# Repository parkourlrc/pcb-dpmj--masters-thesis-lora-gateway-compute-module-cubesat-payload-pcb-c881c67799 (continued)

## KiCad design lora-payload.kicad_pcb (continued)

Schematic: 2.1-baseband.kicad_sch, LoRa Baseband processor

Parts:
C701, C703, C705, C706, C707, C709, C711, C712, C713: 0.1uF; C_0402_1005Metric; PartNumber GRM155R71C104KA88J
C702, C704, C708, C710: 1uF; C_0402_1005Metric; PartNumber GRM155Z71A105KE01J
D701: D_Schottky; D_SOD-882
D702, D703, D704: Green; LED_0402_1005Metric
R701, R704, R705: 47 kOhms; R_0402_1005Metric; PartNumber RC0402FR-0747KL
R702: 10 Ohms; R_0402_1005Metric; PartNumber RC0402FR-0710RL
R703: 100 Ohms; R_0402_1005Metric; PartNumber RC0402FR-07100RL
R706, R708, R709: 680 Ohms; R_0402_1005Metric
R707, R712: 33 Ohms; R_0402_1005Metric; PartNumber AC0402FR-0733RL
R710, R711: 4.7 kOhms; R_0402_1005Metric; PartNumber RC0402FR-074K7L
RN701, RN702: 33 Ohms; R_Array_Convex_4x0603; PartNumber YC164-FR-0733RL
TP701, TP702, TP703, TP704, TP705, TP706, TP707, TP708, TP709, TP710, TP711, TP712: TestPoint; TestPoint_Pad_D1.0mm
U701: SX1302IMLTRT; Semtech SX1302 QFN-68-1EP_7x7mm_P0.35mm_EP5.49x5.49mm_Therm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; PartNumber SX1302IMLTRT

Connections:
+1V2_D: C708.2, C709.2, C710.2, C711.2, C712.2, C713.2, U701.5 (VCC_CORE), U701.23 (VCC_CORE), U701.40 (VCC_CORE), U701.56 (VCC_CORE); also elsewhere on the board
+3V3_D: C702.2, C703.2, C704.2, C705.2, C706.2, C707.2, R701.2, R702.2, R704.2, R710.1, R711.1, U701.14 (VCC_IO), U701.30 (VCC_IO), U701.47 (VCC_IO), U701.61 (VCC_IO); also elsewhere on the board
/1.0-digital/CM5_GPIO6_SX1302_RESET: D701.2 (A); also elsewhere on the board
/1.0-digital/CM5_GPIO23_SX1261_DIO1: U701.54 (GPIO_7); also elsewhere on the board
/1.0-digital/CM5_GPIO26_SX1302_GPIO8: TP709.1, U701.53 (GPIO_8); also elsewhere on the board
/1.0-digital/CM5_GPIO27_SX1302_GPIO6: TP708.1, U701.57 (GPIO_6); also elsewhere on the board
/1.0-digital/CM5_SPI_0_CSN_0_SX1302: R701.1, U701.1 (HOST_CSN); also elsewhere on the board
/1.0-digital/CM5_SPI_0_MISO: R703.2; also elsewhere on the board
/1.0-digital/CM5_SPI_0_MOSI: U701.3 (HOST_MOSI); also elsewhere on the board
/1.0-digital/CM5_SPI_0_SCLK: U701.4 (HOST_SCK); also elsewhere on the board
/2.0-radio/2.1-baseband/CTRL0_RF_EN: R704.1, U701.10 (RADIO_A_CTRL_0/EN_LDO); also elsewhere on the board
/2.0-radio/2.1-baseband/CTRL2_RF_SW: U701.12 (RADIO_A_CTRL_2/EN_PA); also elsewhere on the board
/2.0-radio/2.1-baseband/CTRL3_RADIO_A_~RESET: U701.13 (RADIO_A_CTRL_3/~RESET); also elsewhere on the board
/2.0-radio/2.1-baseband/CTRL4_RF_PA_EN: U701.16 (RADIO_A_CTRL_4/PA_GAIN_0); also elsewhere on the board
/2.0-radio/2.1-baseband/CTRL5_RF_PS_EN: U701.17 (RADIO_A_CTRL_5/PA_GAIN_1)
/2.0-radio/2.1-baseband/CTRL9_RADIO_B_~RESET: U701.28 (RADIO_B_CTRL_9/~RESET); also elsewhere on the board
/2.0-radio/2.1-baseband/RADIO_A_CLK_32M: U701.43 (RADIO_A_CLK_I); also elsewhere on the board
/2.0-radio/2.1-baseband/RADIO_A_CLK_O: R707.1; also elsewhere on the board
/2.0-radio/2.1-baseband/RADIO_A_CSN: U701.68 (RADIO_A_CSN); also elsewhere on the board
/2.0-radio/2.1-baseband/RADIO_A_IQ0: RN701.2 (R2.1); also elsewhere on the board
/2.0-radio/2.1-baseband/RADIO_A_IQ1: RN701.3 (R3.1); also elsewhere on the board
/2.0-radio/2.1-baseband/RADIO_A_IQ2: RN701.4 (R4.1); also elsewhere on the board
/2.0-radio/2.1-baseband/RADIO_A_IQ3: RN701.1 (R1.1); also elsewhere on the board
/2.0-radio/2.1-baseband/RADIO_A_MISO: U701.42 (RADIO_A_MISO); also elsewhere on the board
/2.0-radio/2.1-baseband/RADIO_A_MOSI: U701.67 (RADIO_A_MOSI); also elsewhere on the board
/2.0-radio/2.1-baseband/RADIO_A_SCK: U701.65 (RADIO_A_SCK); also elsewhere on the board
/2.0-radio/2.1-baseband/RADIO_B_CLK_32M: U701.34 (RADIO_A_CLK_I); also elsewhere on the board
/2.0-radio/2.1-baseband/RADIO_B_CLK_O: R712.1; also elsewhere on the board
/2.0-radio/2.1-baseband/RADIO_B_CSN: U701.18 (RADIO_B_CSN); also elsewhere on the board
/2.0-radio/2.1-baseband/RADIO_B_IQ0: RN702.2 (R2.1); also elsewhere on the board
/2.0-radio/2.1-baseband/RADIO_B_IQ1: RN702.3 (R3.1); also elsewhere on the board
/2.0-radio/2.1-baseband/RADIO_B_IQ2: RN702.4 (R4.1); also elsewhere on the board
/2.0-radio/2.1-baseband/RADIO_B_IQ3: RN702.1 (R1.1); also elsewhere on the board
/2.0-radio/2.1-baseband/RADIO_B_MISO: U701.33 (RADIO_B_MISO); also elsewhere on the board
/2.0-radio/2.1-baseband/RADIO_B_MOSI: U701.19 (RADIO_B_MOSI); also elsewhere on the board
/2.0-radio/2.1-baseband/RADIO_B_SCK: U701.21 (RADIO_B_SCK); also elsewhere on the board
/2.0-radio/2.1-baseband/SX1302.RESET: C701.1, D701.1 (K), R705.2, U701.7 (RESET)
/2.0-radio/2.1-baseband/SX1302_CFG_OK: R706.2, TP702.1, U701.66 (GPIO_0)
/2.0-radio/2.1-baseband/SX1302_RX_ON: R709.2, TP706.1, U701.59 (GPIO_4)
/2.0-radio/2.1-baseband/SX1302_TX_ON: R708.2, TP704.1, U701.63 (GPIO_2)
GND: C702.1, C703.1, C704.1, C705.1, C706.1, C707.1, C708.1, C709.1, C710.1, C711.1, C712.1, C713.1, D702.1 (K), D703.1 (K), D704.1 (K), R705.1, U701.6 (GND), U701.8 (PPS), U701.9 (GND), U701.15 (GND), U701.20 (SP_VALID), U701.24 (GND), U701.25 (GND), U701.39 (GND), U701.46 (GND), U701.55 (GND), U701.62 (GND), U701.69 (GND); also elsewhere on the board
unnamed: C701.2, R702.1
unnamed: D702.2 (A), R706.1
unnamed: D703.2 (A), R708.1
unnamed: D704.2 (A), R709.1
unnamed: RN701.8 (R1.2), U701.41 (RADIO_A_IQ_3)
unnamed: RN701.7 (R2.2), U701.44 (RADIO_A_IQ_0)
unnamed: RN701.6 (R3.2), U701.45 (RADIO_A_IQ_1)
unnamed: RN701.5 (R4.2), U701.49 (RADIO_A_IQ_2)
unnamed: RN702.8 (R1.2), U701.32 (RADIO_B_IQ_3)
unnamed: RN702.7 (R2.2), U701.35 (RADIO_B_IQ_0)
unnamed: RN702.6 (R3.2), U701.36 (RADIO_B_IQ_1)
unnamed: RN702.5 (R4.2), U701.38 (RADIO_B_IQ_2)
unnamed: R703.1, U701.2 (HOST_MISO)
unnamed: TP701.1, U701.11 (RADIO_A_CTRL_1/EN_LNA)
unnamed: R707.2, U701.48 (RADIO_A_IQ_4)
unnamed: R712.2, U701.37 (RADIO_B_IQ_4)
unnamed: TP703.1, U701.64 (GPIO_1)
unnamed: TP705.1, U701.60 (GPIO_3)
unnamed: TP707.1, U701.58 (GPIO_5)
unnamed: TP710.1, U701.52 (GPIO_9)
unnamed: R710.2, TP711.1, U701.51 (GPIO_10)
unnamed: R711.2, TP712.1, U701.50 (GPIO_11)

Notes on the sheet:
Pin 14
Pin 61
Pin 56
Enable RFFE PSU (UNUSED)
Enable PA bypass (UNUSED)
(Undocumented)
Pin 30
Pin 47
TX ON
Enable RF frontend (PSU Enable)
Pin 5
Config OK
RX ON
RX/TX switch ctrl (RX=0, TX=1)
LED indicators
Pin 23
(undocumented)
LoRa SX1302 baseband processor
Pin 40
IMPORTANT! Control signals are the same as PCB_E539V03A, which uses the logic inherited from the SKY66420-11 RF Front-End (RFFE): - CSD=0 RFFE shutdown (ALL OFF) [CSD is connected to CTRL0_RF_EN] - CTX=0 RFSW RX mode (LNA ON) [CTX is connected to CTRL2_RF_SW] - CTX=1 RFSW TX mode (LNA OFF) - CPS=0 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

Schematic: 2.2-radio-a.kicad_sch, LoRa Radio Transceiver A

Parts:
C801: 1uF; C_0402_1005Metric; PartNumber GRM155Z71A105KE01J
C802: 0.1uF; C_0402_1005Metric; PartNumber GRM155R71C104KA88J
C803: 0.47 uF; C_0402_1005Metric; PartNumber CGA2B1X7S1C474K050BC
C804: 47 nF; C_0402_1005Metric; PartNumber CC0402JRX7R8BB473
C805: 47 pF; C_0402_1005Metric; PartNumber GRM1555C1H470JA01D
C806: 10 pF; C_0402_1005Metric; PartNumber GRM1555C1H100FA01D
C807: 3.3 pF; C_0402_1005Metric; PartNumber GJM1555C1H3R3WB01D
C808: 39 pF; C_0402_1005Metric; PartNumber GRM1555C1H390FA01J
C809: 5.6 pF; C_0402_1005Metric; PartNumber GRM1555C1H5R6BA01D
C810: 2.2 pF; C_0402_1005Metric; PartNumber GRM1555C2A2R2WA01D
C811: 1 pF; C_0402_1005Metric; PartNumber GRM1555C1H1R0WA01D
C812: 2 pF; C_0402_1005Metric; PartNumber GRM1555C2A2R0WA01D
L801: 15 uH; L_1008_2520Metric; PartNumber VLS252010CX-150M-1
L802: 47 nH; L_0402_1005Metric; PartNumber LQW15AN47NG80D
L803: 2.5 nH; L_0402_1005Metric; PartNumber LQW15AN2N5B0ZD
L804: 4.7 nH; L_0402_1005Metric; PartNumber LQW15AN4N7B0ZD
L805: 16 nH; L_0402_1005Metric; PartNumber LQW15AN16NG00D
L806: 33 nH; L_0402_1005Metric; PartNumber LQW15AN33NG00D
R801: 47 kOhms; R_0402_1005Metric; PartNumber RC0402FR-0747KL
R802: 220 Ohms; R_0402_1005Metric; PartNumber RC0402FR-07220RL
R803: 100 Ohms; R_0402_1005Metric; PartNumber RC0402FR-07100RL
TP801, TP802: TestPoint; TestPoint_Pad_D1.0mm
U801: SX1250IMLTRT; QFN-24-1EP_4x4mm_P0.5mm_EP2.6x2.6mm_ThermalVias; PartNumber SX1250IMLTRT

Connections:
+3V3_RF: C801.2, C802.2, R801.1, U801.2 (VDD_IN), U801.9 (VBAT_RF), U801.10 (VBAT_DIO); also elsewhere on the board
/2.0-radio/2.1-baseband/CTRL3_RADIO_A_~RESET: R801.2, U801.15 (~RESET); also elsewhere on the board
/2.0-radio/2.1-baseband/RADIO_A_CLK_32M: U801.14 (BUSY); also elsewhere on the board
/2.0-radio/2.1-baseband/RADIO_A_CLK_O: U801.11 (DIO5); also elsewhere on the board
/2.0-radio/2.1-baseband/RADIO_A_CSN: U801.18 (SCK); also elsewhere on the board
/2.0-radio/2.1-baseband/RADIO_A_IQ0: U801.13 (DIO1); also elsewhere on the board
/2.0-radio/2.1-baseband/RADIO_A_IQ1: U801.12 (DIO2); also elsewhere on the board
/2.0-radio/2.1-baseband/RADIO_A_IQ2: U801.5 (DIO3); also elsewhere on the board
/2.0-radio/2.1-baseband/RADIO_A_IQ3: U801.21 (DIO4); also elsewhere on the board
/2.0-radio/2.1-baseband/RADIO_A_MISO: R803.2; also elsewhere on the board
/2.0-radio/2.1-baseband/RADIO_A_MOSI: U801.17 (MOSI); also elsewhere on the board
/2.0-radio/2.1-baseband/RADIO_A_SCK: U801.19 (NSS); also elsewhere on the board
/2.0-radio/2.2-radio-a/RADIO_A_RFI: C811.1, L806.1; also elsewhere on the board
/2.0-radio/2.2-radio-a/RADIO_A_RFO: C810.1, L804.1; also elsewhere on the board
/2.0-radio/2.2-radio-a/SX1250.DCC_SW: L801.2, U801.8 (DCC_SW)
/2.0-radio/2.2-radio-a/SX1250.RFI_N: C811.2, L805.1, U801.23 (RFI_N)
/2.0-radio/2.2-radio-a/SX1250.RFI_P: C812.1, L805.2, L806.2, U801.22 (RFI_P)
/2.0-radio/2.2-radio-a/SX1250.RFO: C807.1, L802.2, L803.2, U801.24 (RFO)
/2.0-radio/2.2-radio-a/SX1250.VREG: C803.2, L801.1, U801.6 (VREG)
/2.0-radio/2.2-radio-a/SX1250.VR_PA: C804.2, C805.2, L802.1, TP802.1, U801.1 (VR_PA)
/2.0-radio/2.2-radio-a/SX1250.XTA: C806.2, TP801.1, U801.3 (XTA)
/2.0-radio/TCXO.CLK: R802.2; also elsewhere on the board
GND: C801.1, C802.1, C803.1, C804.1, C805.1, C809.2, C810.2, C812.2, U801.7 (GND), U801.20 (GND), U801.25 (GND); also elsewhere on the board
unnamed: C806.1, R802.1
unnamed: C807.2, C808.2, C809.1, L803.1
unnamed: C808.1, L804.2
unnamed: R803.1, U801.16 (MISO)

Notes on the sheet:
X7S ±10% 16V
C0G ±1% 50V 0402
LoRa Radio A - SX1250 transceiver (TX & RX)
X7R ±10% 16V 0402
X7R ±5% 25V 0402
- DIO1-DIO4: IQ data - DIO5: IQ data clk?
X7R ±10% 10V 0402
C0G 5% 50V 0402
440 mA, 648 mOhm
Shielded, 560 mA, 914 mOhm

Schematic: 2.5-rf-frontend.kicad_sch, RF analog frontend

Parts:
C1101, C1102, C1107, C1108: 0.1uF; C_0402_1005Metric; PartNumber GRM155R71C104KA88J
C1103, C1104, C1105, C1106: 56 pF; C_0402_1005Metric; PartNumber GCM1555C1H560FA16D
D1101: LXES1UTAA1-157; D_SOD-882; PartNumber LXES1UTAA1-157
J1101: Conn_Coaxial; MMCX_Molex_73415-0961_Horizontal_1.6mm-PCB; PartNumber 73415-0961
U1101: 74AHC1G08; SOT-23-5; PartNumber SN74AHC1G08DCK3
U1102: BGS12P2L6; Infineon_PG-TSNP-6-10_0.7x1.1mm_0.7x1.1mm_P0.4mm
U1103: SN74LVC1G00DBV; SOT-23-5; PartNumber SN74LVC1G00DBVR
U1104: SN74LVC1G14DBV; SOT-23-5; PartNumber SN74LVC1G14DBVR

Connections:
+3V3_D: C1101.2, C1107.2, C1108.2, U1101.5 (VCC), U1103.5 (VCC), U1104.5 (VCC); also elsewhere on the board
+3V3_RF: C1102.2, U1102.4 (VDD); also elsewhere on the board
/2.0-radio/2.1-baseband/CTRL0_RF_EN: U1101.2, U1103.1; also elsewhere on the board
/2.0-radio/2.1-baseband/CTRL2_RF_SW: U1102.6 (CTRL), U1104.2; also elsewhere on the board
/2.0-radio/2.1-baseband/CTRL4_RF_PA_EN: U1101.1; also elsewhere on the board
/2.0-radio/2.5-rf-frontend/2.5.1-rf-tx-path/EN_PA: U1101.4; also elsewhere on the board
/2.0-radio/2.5-rf-frontend/2.5.1-rf-tx-path/TX_OUT: C1103.1; also elsewhere on the board
/2.0-radio/2.5-rf-frontend/2.5.2-rf-rx-path/RX: C1106.1; also elsewhere on the board
/2.0-radio/2.5-rf-frontend/2.5.2-rf-rx-path/~EN_LNA: U1103.4; also elsewhere on the board
/2.0-radio/2.5-rf-frontend/2.5.3-rf-filter/P1: C1104.2; also elsewhere on the board
/2.0-radio/2.5-rf-frontend/2.5.3-rf-filter/P2: C1105.1; also elsewhere on the board
/2.0-radio/2.5-rf-frontend/ANT: C1105.2, D1101.2 (A2), J1101.1 (In)
/2.0-radio/2.5-rf-frontend/RFSW.IN: C1104.1, U1102.5 (RFIN)
/2.0-radio/2.5-rf-frontend/RFSW.RX: C1106.2, U1102.3 (RF1)
/2.0-radio/2.5-rf-frontend/RFSW.TX: C1103.2, U1102.1 (RF2)
GND: C1101.1, C1102.1, C1107.1, C1108.1, D1101.1 (A1), J1101.2 (Ext), U1101.3 (GND), U1102.2 (GND), U1103.3 (GND), U1104.3 (GND); also elsewhere on the board
unnamed: U1103.2, U1104.4

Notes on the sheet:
TRANSMIT PATH
~{EN_LNA} = NOT(EN_RF·~{RFSW_CTRL})
RECEIVE PATH
Radio-Frequency Front-End
COMMON RF I/O PATH
MMCX connector (RFIO, 50 ohm)
Low-pass inter-modulation products and harmonic filter
Logic gates to replicate the control logic that the baseband processor expects
ESD protection DC decoupling
RX/TX Switch (@ 868 MHz) Return loss = 27 dB Insertion loss = 0.2 dB Isolation = 45 dB Pin,max = 37 dBm
CTRL=0 : RF1 (RX) CTRL=1 : RF2 (TX)

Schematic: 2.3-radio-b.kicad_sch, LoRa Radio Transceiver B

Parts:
C901: 1uF; C_0402_1005Metric; PartNumber GRM155Z71A105KE01J
C902: 0.1uF; C_0402_1005Metric; PartNumber GRM155R71C104KA88J
C903: 0.47 uF; C_0402_1005Metric; PartNumber CGA2B1X7S1C474K050BC
C904: 10 pF; C_0402_1005Metric; PartNumber GRM1555C1H100FA01D
C905: 1 pF; C_0402_1005Metric; PartNumber GRM1555C1H1R0WA01D
C906: 2 pF; C_0402_1005Metric; PartNumber GRM1555C2A2R0WA01D
L901: 15 uH; L_1008_2520Metric; PartNumber VLS252010CX-150M-1
L902: 16 nH; L_0402_1005Metric; PartNumber LQW15AN16NG00D
L903: 33 nH; L_0402_1005Metric; PartNumber LQW15AN33NG00D
R901: 47 kOhms; R_0402_1005Metric; PartNumber RC0402FR-0747KL
R902: 220 Ohms; R_0402_1005Metric; PartNumber RC0402FR-07220RL
R903: 100 Ohms; R_0402_1005Metric; PartNumber RC0402FR-07100RL
TP901: TestPoint; TestPoint_Pad_D1.0mm
U901: SX1250IMLTRT; QFN-24-1EP_4x4mm_P0.5mm_EP2.6x2.6mm_ThermalVias; PartNumber SX1250IMLTRT

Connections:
+3V3_RF: C901.2, C902.2, R901.1, U901.2 (VDD_IN), U901.9 (VBAT_RF), U901.10 (VBAT_DIO); also elsewhere on the board
/2.0-radio/2.1-baseband/CTRL9_RADIO_B_~RESET: R901.2, U901.15 (~RESET); also elsewhere on the board
/2.0-radio/2.1-baseband/RADIO_B_CLK_32M: U901.14 (BUSY); also elsewhere on the board
/2.0-radio/2.1-baseband/RADIO_B_CLK_O: U901.11 (DIO5); also elsewhere on the board
/2.0-radio/2.1-baseband/RADIO_B_CSN: U901.18 (SCK); also elsewhere on the board
/2.0-radio/2.1-baseband/RADIO_B_IQ0: U901.13 (DIO1); also elsewhere on the board
/2.0-radio/2.1-baseband/RADIO_B_IQ1: U901.12 (DIO2); also elsewhere on the board
/2.0-radio/2.1-baseband/RADIO_B_IQ2: U901.5 (DIO3); also elsewhere on the board
/2.0-radio/2.1-baseband/RADIO_B_IQ3: U901.21 (DIO4); also elsewhere on the board
/2.0-radio/2.1-baseband/RADIO_B_MISO: R903.2; also elsewhere on the board
/2.0-radio/2.1-baseband/RADIO_B_MOSI: U901.17 (MOSI); also elsewhere on the board
/2.0-radio/2.1-baseband/RADIO_B_SCK: U901.19 (NSS); also elsewhere on the board
/2.0-radio/2.3-radio-b/RADIO_B_RFI: C905.1, L903.1; also elsewhere on the board
/2.0-radio/2.3-radio-b/SX1250.DCC_SW: L901.2, U901.8 (DCC_SW)
/2.0-radio/2.3-radio-b/SX1250.RFI_N: C905.2, L902.1, U901.23 (RFI_N)
/2.0-radio/2.3-radio-b/SX1250.RFI_P: C906.1, L902.2, L903.2, U901.22 (RFI_P)
/2.0-radio/2.3-radio-b/SX1250.VREG: C903.2, L901.1, U901.6 (VREG)
/2.0-radio/2.3-radio-b/SX1250.XTA: C904.2, TP901.1, U901.3 (XTA)
/2.0-radio/TCXO.CLK: R902.2; also elsewhere on the board
GND: C901.1, C902.1, C903.1, C906.2, U901.7 (GND), U901.20 (GND), U901.25 (GND); also elsewhere on the board
unnamed: C904.1, R902.1
unnamed: R903.1, U901.16 (MISO)

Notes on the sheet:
- DIO1-DIO4: IQ data - DIO5: IQ data clk?
LoRa Radio B - SX1250 transceiver (RX only)
X7S ±10% 16V
C0G ±1% 50V 0402
Shielded, 560 mA, 914 mOhm
X7R ±10% 10V 0402
X7R ±10% 16V 0402

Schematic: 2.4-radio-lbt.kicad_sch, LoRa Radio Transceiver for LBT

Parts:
C1001: 1uF; C_0402_1005Metric; PartNumber GRM155Z71A105KE01J
C1002: 0.1uF; C_0402_1005Metric; PartNumber GRM155R71C104KA88J
C1003: 0.47 uF; C_0402_1005Metric; PartNumber CGA2B1X7S1C474K050BC
C1004: 10 pF; C_0402_1005Metric; PartNumber GRM1555C1H100FA01D
C1005: 1 pF; C_0402_1005Metric; PartNumber GRM1555C1H1R0WA01D
C1006: 2 pF; C_0402_1005Metric; PartNumber GRM1555C2A2R0WA01D
L1001: 15 uH; L_1008_2520Metric; PartNumber VLS252010CX-150M-1
L1002: 16 nH; L_0402_1005Metric; PartNumber LQW15AN16NG00D
L1003: 33 nH; L_0402_1005Metric; PartNumber LQW15AN33NG00D
R1001, R1004: 47 kOhms; R_0402_1005Metric; PartNumber RC0402FR-0747KL
R1002: 220 Ohms; R_0402_1005Metric; PartNumber RC0402FR-07220RL
R1003: 100 Ohms; R_0402_1005Metric; PartNumber RC0402FR-07100RL
TP1001, TP1002, TP1003, TP1004: TestPoint; TestPoint_Pad_D1.0mm
U1001: SX1261IMLTRT; QFN-24-1EP_4x4mm_P0.5mm_EP2.6x2.6mm

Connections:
+3V3_RF: C1001.2, C1002.2, R1001.1, R1004.2, U1001.1 (VDD_IN), U1001.10 (VBAT), U1001.11 (VBAT_IO); also elsewhere on the board
/1.0-digital/CM5_GPIO4_SX1261_BUSY: U1001.14 (BUSY); also elsewhere on the board
/1.0-digital/CM5_GPIO5_SX1261_~RESET: R1001.2, U1001.15 (~RESET); also elsewhere on the board
/1.0-digital/CM5_GPIO22_SX1261_DIO2: TP1003.1, U1001.12 (DIO2); also elsewhere on the board
/1.0-digital/CM5_GPIO23_SX1261_DIO1: TP1002.1, U1001.13 (DIO1); also elsewhere on the board
/1.0-digital/CM5_SPI_0_CSN_1_SX1261: R1004.1, U1001.19 (NSS); also elsewhere on the board
/1.0-digital/CM5_SPI_0_MISO: R1003.2; also elsewhere on the board
/1.0-digital/CM5_SPI_0_MOSI: U1001.17 (MOSI); also elsewhere on the board
/1.0-digital/CM5_SPI_0_SCLK: U1001.18 (SCK); also elsewhere on the board
/2.0-radio/2.4-radio-lbt/RADIO_LBT_RFI: C1005.1, L1003.1; also elsewhere on the board
/2.0-radio/2.4-radio-lbt/SX1261.DCC_SW: L1001.2, U1001.9 (DCC_SW)
/2.0-radio/2.4-radio-lbt/SX1261.RFI_N: C1005.2, L1002.1, U1001.22 (RFI_N)
/2.0-radio/2.4-radio-lbt/SX1261.RFI_P: C1006.1, L1002.2, L1003.2, U1001.21 (RFI_P)
/2.0-radio/2.4-radio-lbt/SX1261.VREG: C1003.2, L1001.1, U1001.7 (VREG)
/2.0-radio/2.4-radio-lbt/SX1261.XTA: C1004.2, TP1001.1, U1001.3 (XTA)
/2.0-radio/TCXO.CLK: R1002.2; also elsewhere on the board
GND: C1001.1, C1002.1, C1003.1, C1006.2, U1001.2 (GND), U1001.5 (GND), U1001.8 (GND), U1001.20 (GND), U1001.25 (GND); also elsewhere on the board
unnamed: C1004.1, R1002.1
unnamed: TP1004.1, U1001.6 (DIO3)
unnamed: R1003.1, U1001.16 (MISO)

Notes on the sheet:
Shielded, 560 mA, 914 mOhm
X7R ±10% 16V
LoRa Radio LBT - SX1261 transceiver (Listen Before Talk RX only)
C0G ±1% 50V 0402
- DIO1: RxTimeout ? - DIO2: RFSW control ? - DIO3: ValidHeader ?
X7R ±10% 10V
X7S ±10% 16V

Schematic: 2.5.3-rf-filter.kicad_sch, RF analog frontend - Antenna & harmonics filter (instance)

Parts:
C1301: 1.5 pF; C_0402_1005Metric; PartNumber GJM1555C1H1R5BB01D
C1302: 2.7 pF; C_0402_1005Metric; PartNumber GJM1555C1H2R7WB01D
C1303: 3.3 pF; C_0402_1005Metric; PartNumber GJM1555C1H3R3WB01D
C1304: 3.3 pF; C_0402_1005Metric; PartNumber GJM1555C1H3R3CB01D
L1301, L1302: 5.6 nH; L_0402_1005Metric; PartNumber LQW15AN5N6B8ZD

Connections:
/2.0-radio/2.5-rf-frontend/2.5.1-rf-tx-path/PA_FILT.IN: C1301.1, C1302.1, L1301.2; also elsewhere on the board
/2.0-radio/2.5-rf-frontend/2.5.1-rf-tx-path/TX_OUT: C1304.1, L1302.2; also elsewhere on the board
GND: C1302.2, C1303.2, C1304.2; also elsewhere on the board
unnamed: C1301.2, C1303.1, L1301.1, L1302.1

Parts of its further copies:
C1501: 1.5 pF; C_0402_1005Metric; PartNumber GJM1555C1H1R5BB01D
C1502: 2.7 pF; C_0402_1005Metric; PartNumber GJM1555C1H2R7WB01D
C1503: 3.3 pF; C_0402_1005Metric; PartNumber GJM1555C1H3R3WB01D
C1504: 3.3 pF; C_0402_1005Metric; PartNumber GJM1555C1H3R3CB01D
L1501, L1502: 5.6 nH; L_0402_1005Metric; PartNumber LQW15AN5N6B8ZD

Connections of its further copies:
/2.0-radio/2.5-rf-frontend/2.5.3-rf-filter/P1: C1501.1, C1502.1, L1501.2; also elsewhere on the board
/2.0-radio/2.5-rf-frontend/2.5.3-rf-filter/P2: C1504.1, L1502.2; also elsewhere on the board
GND: C1502.2, C1503.2, C1504.2; also elsewhere on the board
unnamed: C1501.2, C1503.1, L1501.1, L1502.1

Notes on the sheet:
C0G ±0.05 pF 50V
RF output path
40 mOhms, ±0.1 nH, 1.7 A
C0G ±0.1 pF 50V
Low-pass inter-modulation products and harmonic filter. Low-pass elliptic filter + LC low-pass - IL = 0.2 dB @ 868 MHz - RL = 15 dB @ 868 MHz - Fc = 1.1 GHz (3 dB) - Transmission zero at 1736 MHz (2*868 MHz)

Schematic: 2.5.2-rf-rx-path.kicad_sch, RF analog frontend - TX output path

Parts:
C1401: 1 uF; C_0402_1005Metric; PartNumber GRM155Z71A105KE01J
C1402: 1000 pF; C_0402_1005Metric; PartNumber GRM1555C1H102FA01D
C1403, C1404: 56 pF; C_0402_1005Metric; PartNumber GCM1555C1H560FA16D
C1405: 3.3 pF; C_0402_1005Metric; PartNumber GJM1555C1H3R3WB01D
L1401: 68 nH; L_0603_1608Metric; PartNumber LQW18AN68NG80D
L1402: 4.2 nH; L_0402_1005Metric; PartNumber LQW15AN4N2B8ZD
L1403: 8.1 nH; L_0402_1005Metric; PartNumber LQW15AN8N1C10D
R1401, R1403: 124 Ohms; R_0402_1005Metric; PartNumber ERA-2AEB1240X
R1402: 127 Ohms; R_1206_3216Metric; PartNumber ERA-8AEB1270V
R1404, R1405: 47 kOhms; R_0402_1005Metric; PartNumber RC0402FR-0747KL
TP1401, TP1402: TestPoint; TestPoint_Pad_D1.0mm
U1401: SCN-3-13+; Mini-Circuits_FV1206-1; PartNumber SCN-3-13+
U1402, U1403: B4377; Filter_1411-5_1.4x1.1mm; PartNumber B39871B4377P810
U1404: QPL9095; DFN-8-1EP_2x2mm_P0.5mm_EP0.8x1.6mm; PartNumber QPL9095SR

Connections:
+4V2_RF: C1401.2, C1402.2, L1401.2, TP1401.1; also elsewhere on the board
/2.0-radio/2.2-radio-a/RADIO_A_RFI: R1402.2, R1403.2, U1401.4 (P3); also elsewhere on the board
/2.0-radio/2.3-radio-b/RADIO_B_RFI: R1401.2, R1403.1, U1401.5 (P2); also elsewhere on the board
/2.0-radio/2.4-radio-lbt/RADIO_LBT_RFI: R1401.1, R1402.1, U1401.6 (P1); also elsewhere on the board
/2.0-radio/2.5-rf-frontend/2.5.2-rf-rx-path/LNA.BYP: R1404.1, U1404.4 (V_{BYP})
/2.0-radio/2.5-rf-frontend/2.5.2-rf-rx-path/LNA.I: L1403.1, U1404.2 (RFI)
/2.0-radio/2.5-rf-frontend/2.5.2-rf-rx-path/LNA.MA: C1404.1, L1403.2
/2.0-radio/2.5-rf-frontend/2.5.2-rf-rx-path/LNA.O: C1403.2, U1404.7 (RFO)
/2.0-radio/2.5-rf-frontend/2.5.2-rf-rx-path/LNA.VDD: L1401.1, U1404.8 (V_{DD})
/2.0-radio/2.5-rf-frontend/2.5.2-rf-rx-path/RX: U1403.1 (I); also elsewhere on the board
/2.0-radio/2.5-rf-frontend/2.5.2-rf-rx-path/SAW1: C1404.2, U1403.4 (O)
/2.0-radio/2.5-rf-frontend/2.5.2-rf-rx-path/SAW2: C1403.1, U1402.1 (I)
/2.0-radio/2.5-rf-frontend/2.5.2-rf-rx-path/SPLT.IN: C1405.2, L1402.1, U1401.2 (SUM)
/2.0-radio/2.5-rf-frontend/2.5.2-rf-rx-path/SPLT.MA: L1402.2, U1402.4 (O)
/2.0-radio/2.5-rf-frontend/2.5.2-rf-rx-path/~EN_LNA: R1405.1, TP1402.1, U1404.5 (V_{SD}); also elsewhere on the board
GND: C1401.1, C1402.1, C1405.1, R1404.2, R1405.2, U1401.1 (GND), U1401.3 (GND), U1402.2 (GND), U1402.3 (GND), U1402.5 (GND), U1403.2 (GND), U1403.3 (GND), U1403.5 (GND), U1404.1 (GND), U1404.3 (NC), U1404.6 (GND), U1404.9 (GND); also elsewhere on the board

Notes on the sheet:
X7R ±10% 10V 0402
44 mOhms, ±0.1 nH
380 mOhms ±2% 630 mA
±0.1% 25ppm 0603 0.10W
±0.1% 25ppm 1206 0.25W
70 mOhms, ±0.2 nH
C0G ±1% 50V 0402
RF input path
C0G ±0.05 pF 50V
Splitter matching network (LC)
Symmetrical power splitter IL=5 dB
SAW NB filter IL=1.5 dB
The LNA may NOT be bypassed, but it can be turned off to save energy
V_{BYP}=0 Bypass OFF V_{SD}=0 LNA ON V_{SD}=1 LNA OFF
S parameters of the RX chain, from the antenna port (port 1) to one output of the 3-1 splitter (port 2)
LNA matching network (L)
LNA G=22 dB NF=0.6 dB
Caution during assembly! Index Area is on the opposite side of the pin 1. See datasheet.

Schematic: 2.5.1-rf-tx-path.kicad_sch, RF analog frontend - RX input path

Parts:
C1201: 47 pF; C_0402_1005Metric; PartNumber GRM1555C1H470JA01D; not fitted
C1202: 10 uF; C_0805_2012Metric; PartNumber GRT21BC71E106KE13K; not fitted
C1203, C1205, C1208, C1209: 10 nF; C_0402_1005Metric
C1204: 10uF; C_0805_2012Metric; PartNumber GRT21BC71E106KE13K
C1206: 47 pF; C_0402_1005Metric; PartNumber GRM1555C1H470JA01D
C1207: 56 pF; C_0402_1005Metric; PartNumber GCM1555C1H560FA16D
C1210, C1212: 1 uF; C_0402_1005Metric; PartNumber GRM155Z71A105KE01J
C1211: 1 uF; C_0402_1005Metric; PartNumber GRM155Z71A105KE01J; not fitted
L1201: 33 nH; L_0603_1608Metric; PartNumber LQW18AN33NG80D
R1201, R1202: 270 Ohms; R_0402_1005Metric; PartNumber RC0402FR-07270RL
R1203: 47 kOhms; R_0402_1005Metric; PartNumber RC0402FR-0747KL
TP1201, TP1202, TP1203: TestPoint; TestPoint_Pad_D1.0mm
U1201: B4377; Filter_1411-5_1.4x1.1mm; PartNumber B39871B4377P810
U1202: CMX90A004; QFN-16-1EP_4x4mm_P0.65mm_EP2.7x2.7mm_ThermalVias; PartNumber CMX90A004
U1203: TPS22917DBV; SOT-23-6

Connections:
+3V3_RF: C1210.2, C1211.2, C1212.2, U1202.6 (V_{BIAS1}), U1202.7 (V_{BIAS2}), U1203.1 (VIN); also elsewhere on the board
+3V6_RF: C1201.2, C1202.2, C1203.2, C1204.2, C1205.2, C1206.2, L1201.2, TP1201.1, U1202.16 (V_{CC1}); also elsewhere on the board
/2.0-radio/2.2-radio-a/RADIO_A_RFO: U1201.1 (I); also elsewhere on the board
/2.0-radio/2.5-rf-frontend/2.5.1-rf-tx-path/EN_PA: TP1203.1, U1203.3 (ON); also elsewhere on the board
/2.0-radio/2.5-rf-frontend/2.5.1-rf-tx-path/PA.IN: U1201.4 (O), U1202.2 (IN)
/2.0-radio/2.5-rf-frontend/2.5.1-rf-tx-path/PA.OUT: C1207.1, U1202.11 (OUT)
/2.0-radio/2.5-rf-frontend/2.5.1-rf-tx-path/PA.VCTRL: C1208.2, C1209.2, R1201.2, R1202.2, R1203.1, TP1202.1, U1203.5 (QOD), U1203.6 (VOUT)
/2.0-radio/2.5-rf-frontend/2.5.1-rf-tx-path/PA.VDD: L1201.1, U1202.13 (V_{CC2b}), U1202.14 (V_{CC2a})
/2.0-radio/2.5-rf-frontend/2.5.1-rf-tx-path/PA.VREF1: R1201.1, U1202.5 (V_{REF1})
/2.0-radio/2.5-rf-frontend/2.5.1-rf-tx-path/PA.VREF2: R1202.1, U1202.8 (V_{REF2})
/2.0-radio/2.5-rf-frontend/2.5.1-rf-tx-path/PA_FILT.IN: C1207.2; also elsewhere on the board
GND: C1201.1, C1202.1, C1203.1, C1204.1, C1205.1, C1206.1, C1208.1, C1209.1, C1210.1, C1211.1, C1212.1, R1203.2, U1201.2 (GND), U1201.3 (GND), U1201.5 (GND), U1202.1 (NC), U1202.3 (NC), U1202.4 (NC), U1202.9 (NC), U1202.10 (NC), U1202.12 (NC), U1202.15 (GND), U1202.17 (GND), U1203.2 (GND); also elsewhere on the board

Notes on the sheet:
RF output path
110 mOhms ±2% 1.1 A
Power switch for shutting down the PA
SAW NB filter IL=1.5 dB
S parameters of the TX chain, from TX_IN (port 1) to TX_OUT (port 2)
Low-pass inter-modulation products and harmonic filter
PA will dissipate around 2.5 W at maximum P_{OUT}
DC blocking capacitor included in PA input
P_{OUT} <= 33 dBm
T_{rise} = 65 ns (From datasheet, without C_{T}) T_{fall} = 2.2 x (R_{DIS} || R_L) x C_L = 20-30 us aprox R_{DIS} = R_{PD} + R_{QOD} == R_{PD} = 750-850 kOhm aprox C_L = 20-30 nF aprox (PA's V_{REF} capacitors) R_L = 500 ohm aprox (V_{REF1} || V_{REF2}) Internal R_{PD} = 750-850 kOhm, external R_{Q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
P_{IN} <= 5 dBm

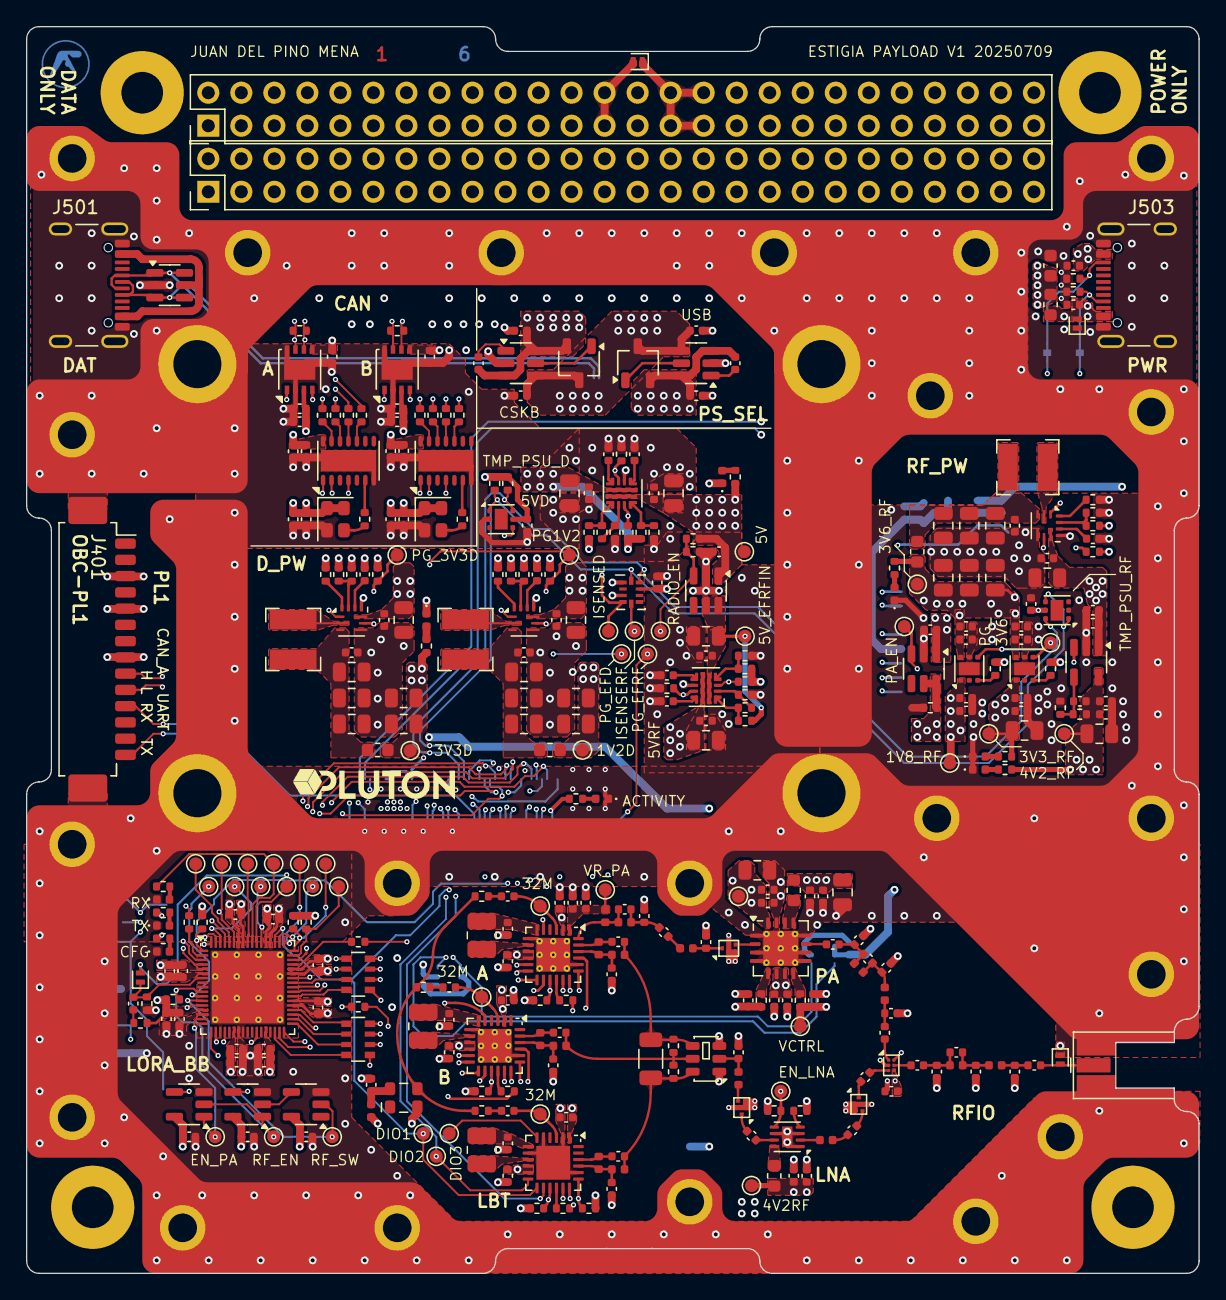
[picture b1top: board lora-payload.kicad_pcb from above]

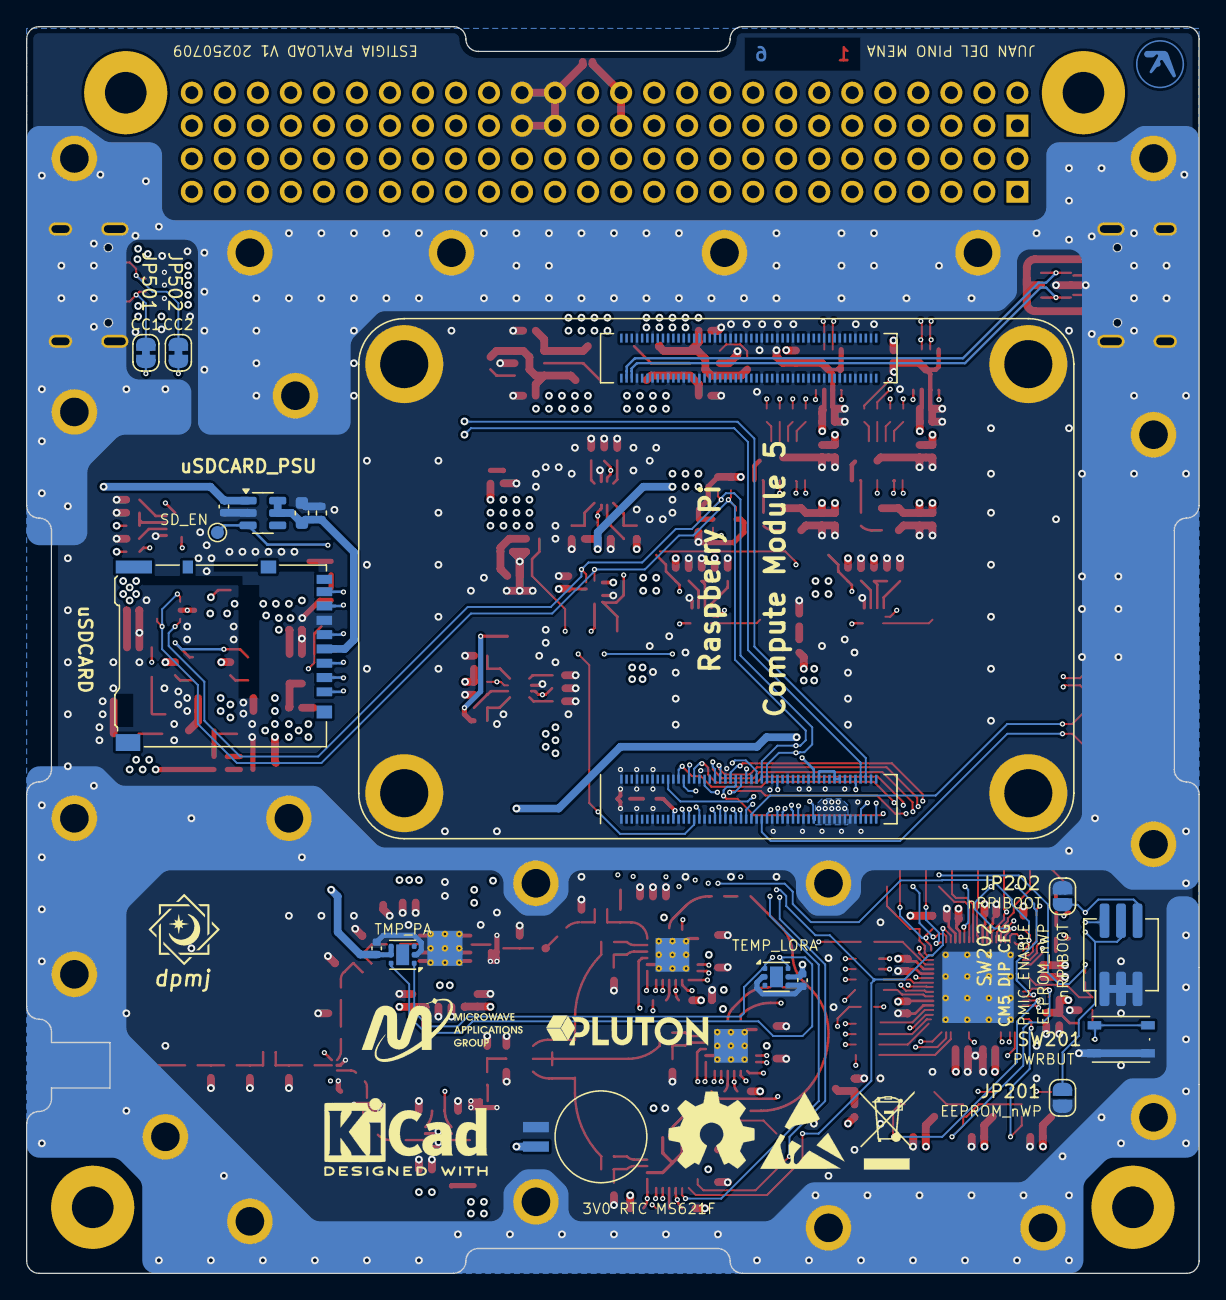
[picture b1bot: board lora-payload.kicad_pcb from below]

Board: 6 copper layers, 90.2 x 95.9 mm, 392 parts (18 on the bottom side), 235 nets.

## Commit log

2025-09-22 add sources
2025-09-22 license
